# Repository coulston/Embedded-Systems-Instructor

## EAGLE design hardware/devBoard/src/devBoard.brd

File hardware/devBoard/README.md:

# Ordering Process for Development Boards

This file outlines a procedure to order development boards from [PCBWay](https://www.pcbway.com/).  
>[!NOTE] 
>These instructions referece manufacturer web pages that are not under my control.  As a 
result the web interfaces may be modified changing the look and feel of the interface.  In this
event, you will need to adapt the instructions to the current interface.

## Step 1: Verify BOM through Digikey
You will be providing PCBWay with the bill of materials (BOM) using parts
found on Digikey.  It is possible that the parts in the existing 
[BOM](https://github.com/coulston/Embedded-Systems-Instructor/blob/main/manufacture/hardware/devBoard%20BOM.xlsx) 
contains parts that are out of stock or have become obselete
since the last order.  Resolving these issues before sending the BOM to 
PCBWay will eliminate a lot of back-and-forth.

1. Login to [DigiKey](https://www.digikey.com/).
2. Start a new cart by clicking on the cart icon in the upper right corner of the web page.
3. Upload the
[BOM](https://github.com/coulston/Embedded-Systems-Instructor/blob/main/hardware/devBoard/manufacture/devBoard%20BOM.xlsx)
file via drag-and-drop of browse for BOM.

4. In the Upload File Mapping pop-up ensure that the manufacturer part number and DigiKey part number pull-downs
are selecting the correct columns of the BOM as shown in the following image.  Not as important, you may want
to select qualtity in the shown column.  In order to scoll horziontally, you will need to first scroll to the
bottom of the window using the control in the right side of the window.  Click on the Add to Current Cart
button when yoy have verified these selections.

5. If there are any issues, they will appear in the shooping cart as errors.

6. If you have obselete parts as shown, you will need to find a suitable replacement
   part from Digikey.  you must ensure that the replacement part has the same footprint, pinout and
   performs the same function as the obselete part.  Since Digikey keeps the technical documents for
   obselete parts, you should be able to get all the needed technical information
   to start this process.

## Step 2: Order from PCBWay

1. Login to [PCBWay](https://www.pcbway.com/).
2. Click on the PCB Assembly icon at the top of the page
3. In the **Assembly Service** area:
   - Quantity: Whatever you need, in this case 50.
   - Do you accept alternatives/substitutes made in China?  Yes

4. Expand **Other Parameters options**. Fill in the text boxes with the values shown below.

5. Expand **PCB Specifications options**.  Fill in the text boxes with the values shown below.
   - Size: 65.28mm x 55.83mm
   - Quantity: Match quantity in step 3.
   - Leave all the following options alone.

6. Scroll to the bottom of the page and click calculate
7. The right side of the web page will update the cost.
   - Click **Save To Cart**
   - Agree to the Special Notes

8.In the upload files pop-up
>[!NOTE] 
>The files are at the links provided.  Download the files to your local machine by clicking on the download raw file
>icon  in the upper right of the window.
- Click **Upload Gerber file** and upload. 
  [Gerber zip](https://github.com/coulston/Embedded-Systems-Instructor/blob/main/hardware/devBoard/manufacture/devBoard.zip)
- Click **Part List (BOM) Upload** and upload
  [BOM excel](https://github.com/coulston/Embedded-Systems-Instructor/blob/main/hardware/devBoard/manufacture/devBoard%20BOM.xlsx)
- Click **Upload Centroid File** and upload
  [Centroid excel](https://github.com/coulston/Embedded-Systems-Instructor/blob/main/hardware/devBoard/manufacture/devBoard%20CPL.xlsx)
- 

9. Click Submitt Order Now
10. You should hear back from the PCBWay engineers in 48 hours.

## Step 3: SD Card Holder
As ordered, the development boards do not come with the SD Cards because they are mounted to the bottom of the 
board. Hence, these have to be ordred and hand soldered using the following instructions.
1. Order 1 SD Card holder fro each development board from [DigiKey] (http://www.digikey.com) part number WM12834CT-ND
2. Solder the SD card holder
- Solder the 9 pins
- Solder the 4 mounting tabs (essential)

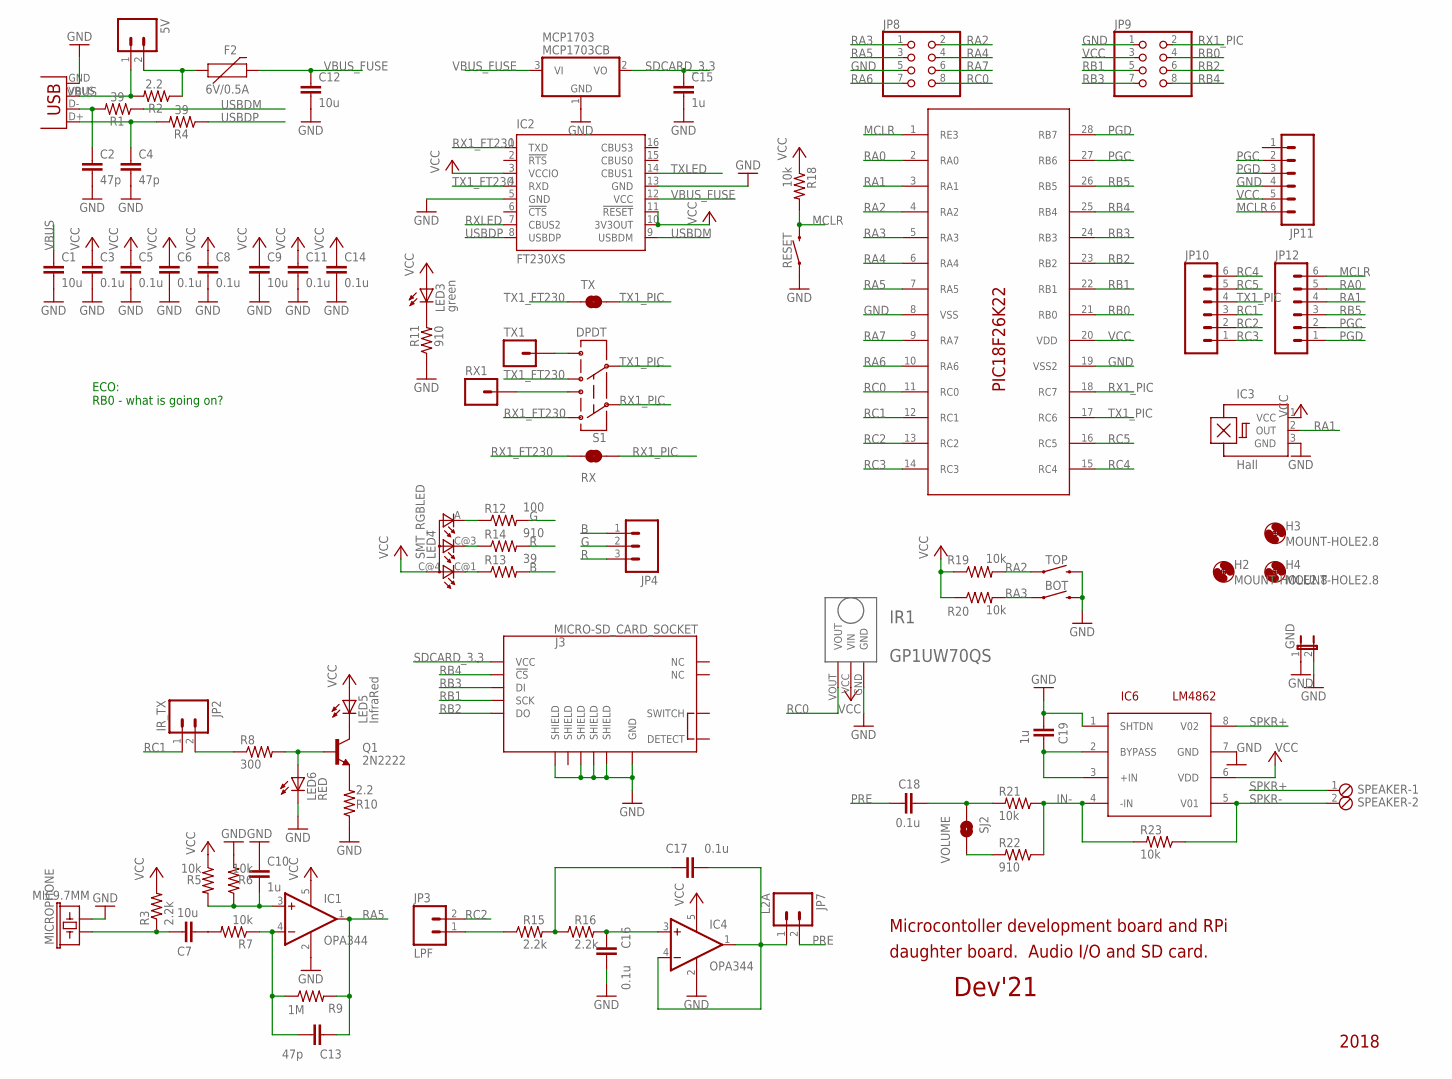
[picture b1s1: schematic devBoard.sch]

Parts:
5V: M02LOCK; 1X02_LOCK
BOT: MOMENTARY-SWITCH-SPST-SMD-5.2MM; TACTILE_SWITCH_SMD_5.2MM
C1, C7, C9, C12: 10u; C1206
C2, C4, C13: 47p; C1206
C3, C5, C6, C8, C11, C14, C16, C17, C18: 0.1u; C1206
C10, C15, C19: 1u; C1206
F2: 6V/0.5A; 1206
GND: JP1E; JP1
H2, H3, H4: MOUNT-HOLE2.8; 2,8
IC1, IC4: OPA344; SOT23-5
IC2: FT230XS; SSOP16
IC3: Hall; SOT23-W
IC6: LM4862; SO08
IR1: GP1UW70QS
J3: MICRO-SD_CARD_SOCKET; MICRO-SD-SOCKET
JP2: IR_TX; 1X02_LOCK
JP3: LPF; 1X02_LOCK
JP4: M03LOCK; 1X03_LOCK
JP7: L2A; 1X02_LOCK
JP8, JP9: PINHD-2X4; 2X04
JP10, JP11, JP12: M06LOCK; 1X06_LOCK
LED3: green; LED-1206
LED4: SMT_RGBLED; P-LCC-4
LED5: InfraRed; LED-1206
LED6: RED; LED-1206
MCP1703: MCP1703CB; SOT23
MICROPHONE: MIC9.7MM; MIC-9.7MM
PIC18F26K22: PIC18F26J2228SSOP; SSOP28DB
Q1: 2N2222; SOT23-3
R1, R4, R13: 39; R1206
R2, R10: 2.2; R1206
R3, R15, R16: 2.2k; R1206
R5, R6, R7, R18, R19, R20, R21, R23: 10k; R1206
R8: 300; R1206
R9: 1M; R1206
R11, R14, R22: 910; R1206
R12: 100; R1206
RESET: MOMENTARY-SWITCH-SPST-SMD-5.2MM; TACTILE_SWITCH_SMD_5.2MM
RX: SJ_NC; SMT-JUMPER_2_NC_TRACE_NO-SILK
RX1: M01PTH; 1X01
S1: DPDT; AYZ0202
SJ2: VOLUME; SJ_2S-NOTRACE
SPEAKER: MPT2; 2POL254
TOP: MOMENTARY-SWITCH-SPST-SMD-5.2MM; TACTILE_SWITCH_SMD_5.2MM
TX: SJ_NC; SMT-JUMPER_2_NC_TRACE_NO-SILK
TX1: M01PTH; 1X01
X1: USBSMD; USB-MINIB

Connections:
B: JP4.1, R13.2
G: JP4.2, R12.2
GND: BOT.3 (2), C1.2, C2.2, C3.2, C4.2, C5.2, C6.2, C8.2, C9.2, C10.1, C11.2, C12.2, C14.2, C15.2, C16.1, C19.2, GND.1, GND.2, IC1.2 (V-), IC2.5 (GND), IC2.13 (GND), IC3.3 (GND), IC4.2 (V-), IC6.1 (SHTDN), IC6.7 (GND), IR1.GND, J3.GND, J3.SHIELD1 (SHIELD), J3.SHIELD3 (SHIELD), J3.SHIELD4 (SHIELD), J3.SHIELD5 (SHIELD), JP8.5, JP9.1, JP11.4, LED6.C, MCP1703.1 (GND), MICROPHONE.2, PIC18F26K22.8 (VSS), PIC18F26K22.19 (VSS2), R6.2, R10.1, R11.1, RESET.1, TOP.3 (2), X1.GND
IN-: IC6.4 (-IN), R21.1, R22.1, R23.2
MCLR: JP11.6, JP12.6, PIC18F26K22.1 (RE3), R18.2, RESET.3 (2)
MIC: C13.1, IC1.4 (-IN), R7.1, R9.1
unnamed: C16.2, IC4.3 (+IN), R16.2
unnamed: C17.2, R15.2, R16.1
unnamed: C17.1, IC4.1 (OUT), IC4.4 (-IN), JP7.1
unnamed: JP3.1, R15.1
unnamed: LED4.C@3 (CBLUE), R14.1
unnamed: C2.1, R1.2, X1.D-
unnamed: C4.1, R4.2, X1.D+
unnamed: C7.1, MICROPHONE.1, R3.1
unnamed: C7.2, R7.2
unnamed: 5V.2, F2.1, R2.1
unnamed: C10.2, IC1.3 (+IN), R5.2, R6.1
unnamed: RX1.1, S1.3
unnamed: LED4.C@1 (CRED), R13.1
unnamed: LED4.A (CGREEN), R12.1
unnamed: LED5.C, Q1.3 (C)
unnamed: LED3.C, R11.2
unnamed: Q1.2 (E), R10.2
unnamed: LED6.A, Q1.1 (B), R8.2
unnamed: C19.1, IC6.2 (BYPASS), IC6.3 (+IN)
unnamed: JP2.2, R8.1
unnamed: S1.6, TX1.1
unnamed: C18.1, R21.2, SJ2.1
unnamed: R22.2, SJ2.2
PGC: JP11.2, JP12.2, PIC18F26K22.27 (RB6)
PGD: JP11.3, JP12.1, PIC18F26K22.28 (RB7)
PRE: C18.2, JP7.2
R: JP4.3, R14.2
RA0: JP12.5, PIC18F26K22.2 (RA0)
RA1: IC3.2 (OUT), JP12.4, PIC18F26K22.3 (RA1)
RA2: JP8.2, PIC18F26K22.4 (RA2), R19.2, TOP.1
RA3: BOT.1, JP8.1, PIC18F26K22.5 (RA3), R20.2
RA4: JP8.4, PIC18F26K22.6 (RA4)
RA5: C13.2, IC1.1 (OUT), JP8.3, PIC18F26K22.7 (RA5), R9.2
RA6: JP8.7, PIC18F26K22.10 (RA6)
RA7: JP8.6, PIC18F26K22.9 (RA7)
RB0: JP9.4, PIC18F26K22.21 (RB0)
RB1: J3.SCLK (SCK), JP9.5, PIC18F26K22.22 (RB1)
RB2: J3.DO, JP9.6, PIC18F26K22.23 (RB2)
RB3: J3.DI, JP9.7, PIC18F26K22.24 (RB3)
RB4: J3.CS (!CS), JP9.8, PIC18F26K22.25 (RB4)
RB5: JP12.3, PIC18F26K22.26 (RB5)
RC0: IR1.VOUT, JP8.8, PIC18F26K22.11 (RC0)
RC1: JP2.1, JP10.3, PIC18F26K22.12 (RC1)
RC2: JP3.2, JP10.2, PIC18F26K22.13 (RC2)
RC3: JP10.1, PIC18F26K22.14 (RC3)
RC4: JP10.6, PIC18F26K22.15 (RC4)
RC5: JP10.5, PIC18F26K22.16 (RC5)
RX1_FT230: IC2.1 (TXD), RX.1, S1.1
RX1_PIC: JP9.2, PIC18F26K22.18 (RC7), RX.2, S1.2
RXLED: IC2.7 (CBUS2)
SDCARD_3.3: C15.1, J3.VCC, MCP1703.2 (VO)
SPKR+: IC6.8 (V02), SPEAKER.1
SPKR-: IC6.5 (V01), R23.1, SPEAKER.2
TX1_FT230: IC2.4 (RXD), S1.4, TX.1
TX1_PIC: JP10.4, PIC18F26K22.17 (RC6), S1.5, TX.2
TXLED: IC2.14 (CBUS1)
USBDM: IC2.9 (USBDM), R1.1
USBDP: IC2.8 (USBDP), R4.1
VBUS: 5V.1, C1.1, R2.2, X1.VBUS
VBUS_FUSE: C12.1, F2.2, IC2.12 (VCC), MCP1703.3 (VI)
VCC: C3.1, C5.1, C6.1, C8.1, C9.1, C11.1, C14.1, IC1.5 (V+), IC2.3 (VCCIO), IC2.10 (3V3OUT), IC2.11 (!RESET), IC3.1 (VCC), IC4.5 (V+), IC6.6 (VDD), IR1.VCC (VIN), JP9.3, JP11.5, LED3.A, LED4.C@4 (A), LED5.A, PIC18F26K22.20 (VDD), R3.2, R5.1, R18.1, R19.1, R20.1

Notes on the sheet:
Microcontoller development board and RPi
daughter board. Audio I/O and SD card.
2018
Dev'21
ECO: RB0 - what is going on?

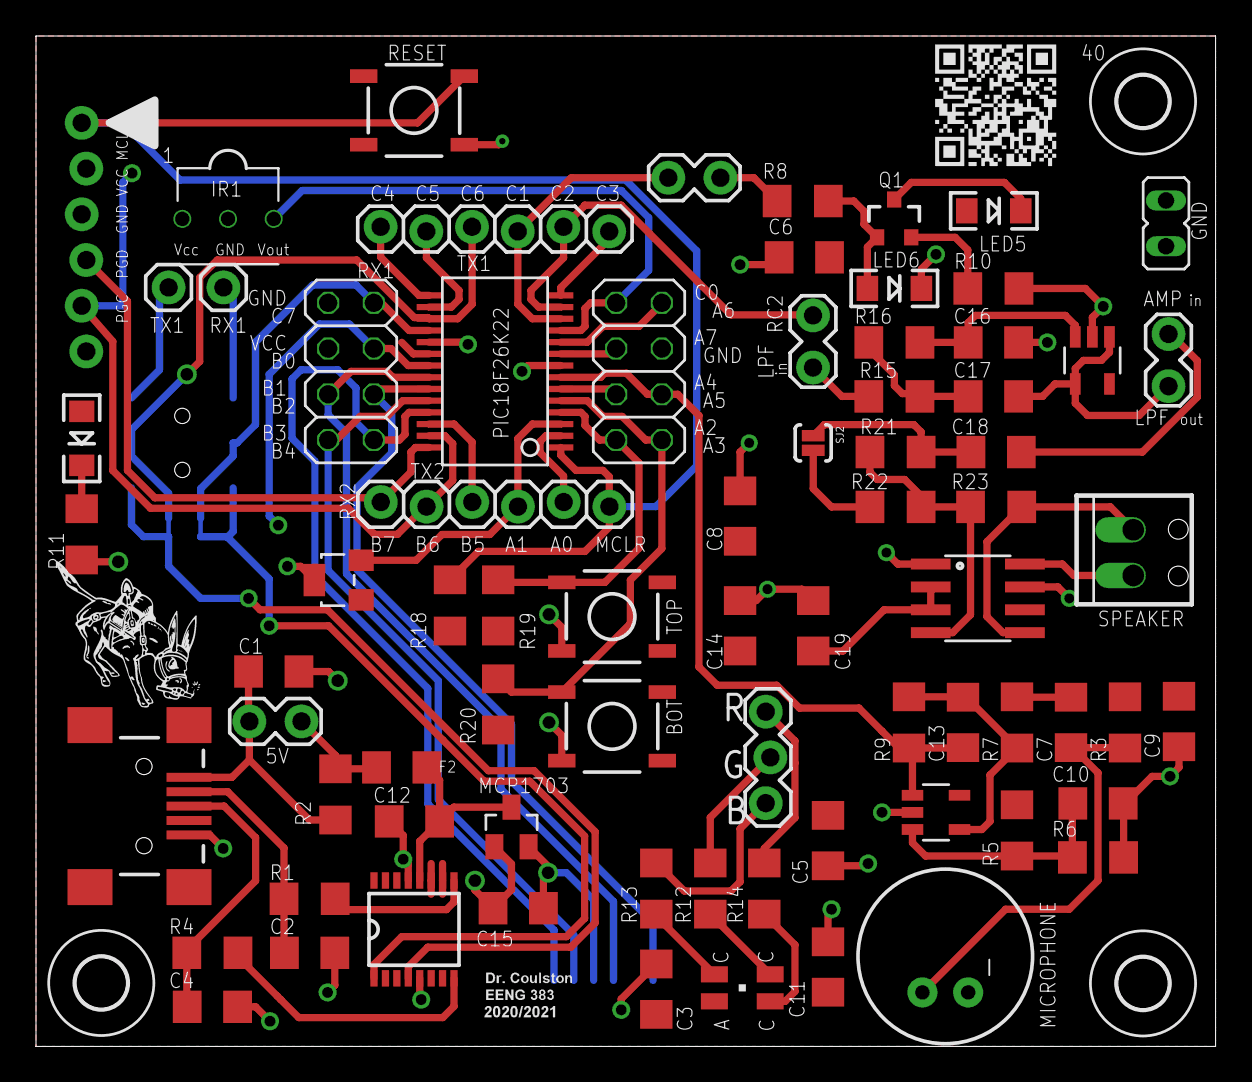
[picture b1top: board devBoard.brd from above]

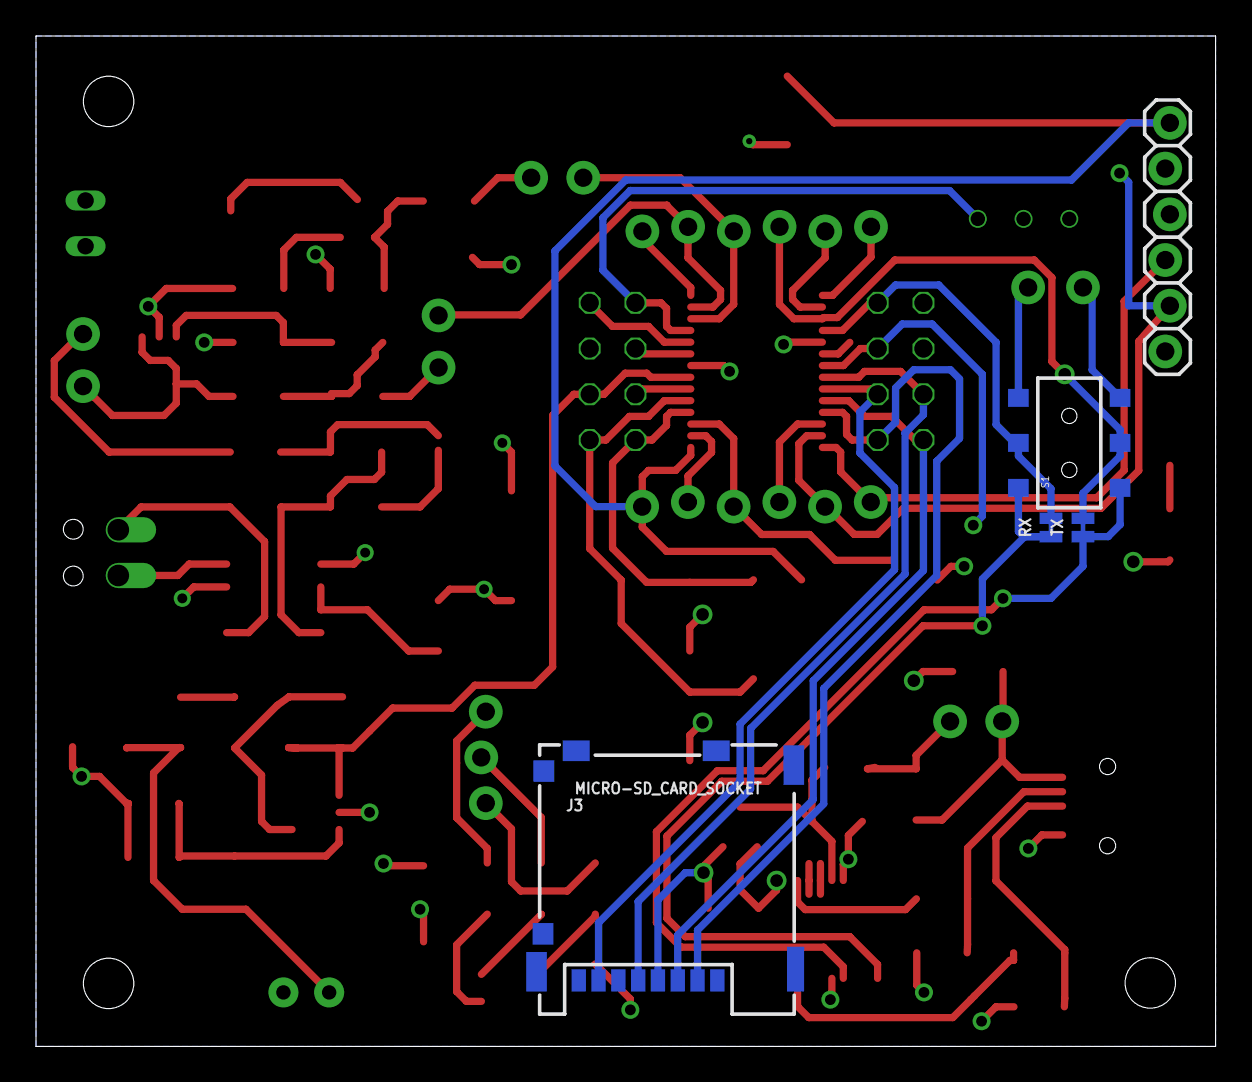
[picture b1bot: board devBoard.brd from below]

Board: 2 copper layers, 65.5 x 56.1 mm, 82 parts (5 on the bottom side), 65 nets.

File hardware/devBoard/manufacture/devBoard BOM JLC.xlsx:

Comment | Designator | Footprint | Part | Quantity
2.2 ohm | R2, R10 | 1206R | C2907445 | 1
39 ohm | R1, R4, R13 | 1206R | C25379 | 1
100 ohms | R12 | 1206R | C17901 | 1
300 ohm | R8 | 1206R | C17887 | 1
910 ohm | R11, R14, R22 | 1206R | C2930433 | 1
2.2k ohm | R3, R15, R16 | 1206R | C17948 | 1
10k ohm | R5, R6, R7, R18, R19, R20, R21, R23 | 1206R | C17902 | 1
1M ohm | R9 | 1206R | C17927 | 1
PTC fuse | F2 | 1206R | C883127 | 1
47pF | C2, C4, C13 | 1206C | C5137553 | 1
0.1uF | C3, C5, C6, C8, C11, C14, C16, C17, C18 | 1206C | C24497 | 1
1uF | C10, C15, C19 | 1206C | C1848 | 1
10uF | C1, C7, C9, C12 | 1206C | C13585 | 1
Tactile Switch SPST-NO Top Actuated Surface Mount | BOT, RESET, TOP | 5.2*5.2 | C5342990 | 1
USB | X1 | Custom | C91144 | 1
PIC 18F25K22 | PIC18F25K22 | SSOP-28 | C51680 | 1
Serial USB bridge | IC2 | SSOP-16 | C69082 | 1
GP Opamp | IC1, IC4 | SOT23-5 | C131974 | 1
2N2222 NPN | Q1 | SOT-23 |  | 1
Linear Voltage Regulator IC 1 Output 250mA SOT-23A-3 | MCP1703 | SOT-23 | C50754 | 1
Audio Amp | IC6 | SOIC-8 | C2860743 | 1
Green SM | LED3 | 1206D | C2984261 | 1
Red SM | LED6 | 1206D | C2984261 | 1
IR LED | LED5 | 1206D |  | 1
RGB LED | LED4 | PLCC-4 | C5355897 | 1
Hall Effect | IC3 | SOT-23-3 | C962159 | 1

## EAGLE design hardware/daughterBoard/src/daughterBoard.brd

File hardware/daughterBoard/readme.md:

# Ordering Process for Daughter Boards

This file outlines a procedure to order development boards from [JLCPCB](https://www.jlcpcb.com/).  
>[!NOTE] 
>These instructions referece manufacturer web pages that are not under my control.  As a 
result the web interfaces may be modified changing the look and feel of the interface.  In this
event, you will need to adapt the instructions to the current interface.

## Order from JLCPCB

1. Download [daughterBoardGerber.zip](Https://github.com/coulston/Embedded-Systems-Instructor/blob/main/hardware/daughterBoard/manufacture/daughterBoardGerber.zip) to your local drive
5. Sign In to [JLCPCB](https://www.jlcpcb.com/).
6. Click on the white Order Now button at the top of the page
7. Click on the blue Add gerber files button
8. In the pop-up, navigate and select daughterBoardGerber.zip you downloaded
9. Leave all the defaults along with the exception:
   - Quantity: Whatever you need
   - PCB Color: Blue has been the standard color
10. Click on the blue Add to Cart button
11. Click on the shopping cart icon at the top of the screen
12. Click the blue Secure Checkout button and proceed with payment and shipping.
13. You should hear back from the JLCPCB in 24 hours.

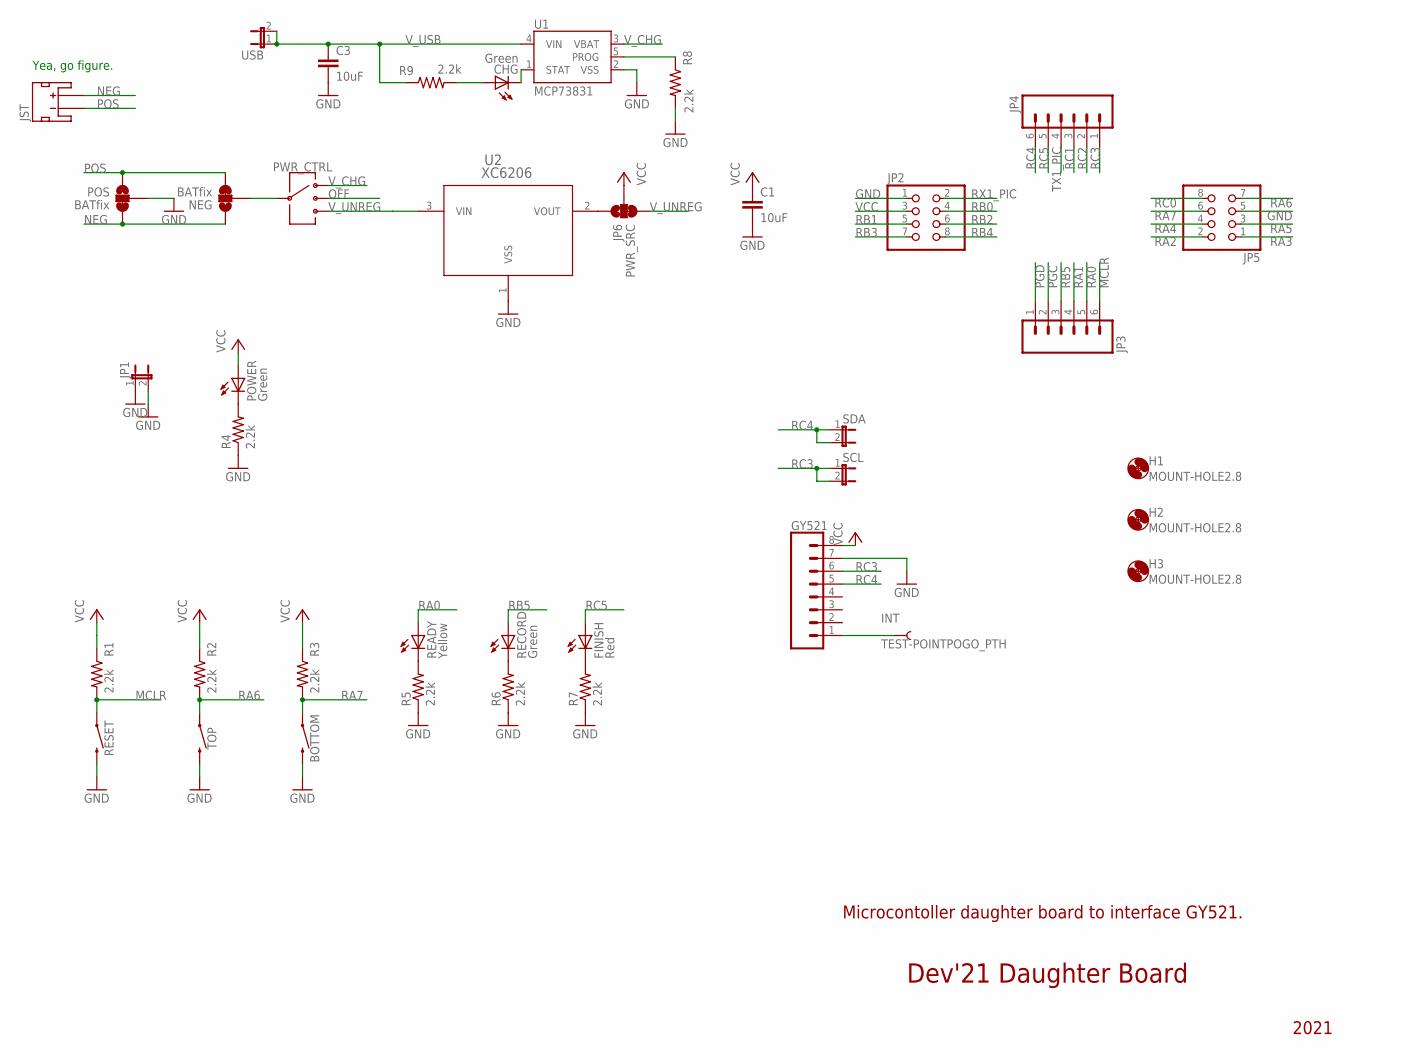
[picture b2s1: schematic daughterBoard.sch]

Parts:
BOTTOM: BOTTOM; TACTILE_SWITCH_SMD_5.2MM
C1, C3: 10uF; C1206
CHG: Green; LED-1206
FINISH: Red; LED-1206
GY521: CONN_08LOCK_LONGPADS; 1X08_LOCK_LONGPADS
H1, H2, H3: MOUNT-HOLE2.8; 2,8
INT: TEST-POINTPOGO_PTH; 1X01_NO_SILK
JP1: JP1E; JP1
JP2, JP5: PINHD-2X4; 2X04
JP3, JP4: M06LOCK; 1X06_LOCK
JP6: PWR_SRC; SMT-JUMPER_3_1-NC_TRACE_SILK
JST: JST_2MM_MALE; JST-2-SMD
NEG: BATfix; SMT-JUMPER_3_1-NC_TRACE_SILK
POS: BATfix; SMT-JUMPER_3_1-NC_TRACE_SILK
POWER: Green; LED-1206
PWR_CTRL: SWITCH-SP3T-SMD; SWITCH_SP3T_SMD
R1, R2, R3, R4, R5, R6, R7, R8, R9: 2.2k; R1206
READY: Yellow; LED-1206
RECORD: Green; LED-1206
RESET: RESET; TACTILE_SWITCH_SMD_5.2MM
SCL: JUMPER-2PTH_LOCK; 1X02_LOCK
SDA: JUMPER-2PTH_LOCK; 1X02_LOCK
TOP: TOP; TACTILE_SWITCH_SMD_5.2MM
U1: MCP73831; SOT23-5
U2: XC6206; SOT-23_TOR-M
USB: JUMPER-2PTH_LOCK; 1X02_LOCK

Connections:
GND: BOTTOM.3 (2), C1.2, C3.2, GY521.7, JP1.1, JP1.2, JP2.1, JP5.5, POS.2, R4.1, R5.1, R6.1, R7.1, R8.2, RESET.3 (2), TOP.3 (2), U1.2 (VSS), U2.1 (VSS)
MCLR: JP3.6, R1.2, RESET.1
unnamed: NEG.2, PWR_CTRL.3
unnamed: R6.2, RECORD.C
unnamed: R5.2, READY.C
unnamed: FINISH.C, R7.2
unnamed: POWER.C, R4.2
unnamed: GY521.1, INT.1
unnamed: JP6.1, U2.2 (VOUT)
unnamed: CHG.A, R9.2
unnamed: R8.1, U1.5 (PROG)
unnamed: CHG.C, U1.1 (STAT)
NEG: JST.2 (+), NEG.1, POS.3
OFF: PWR_CTRL.2
PGC: JP3.2
PGD: JP3.1
POS: JST.1 (-), NEG.3, POS.1
RA0: JP3.5, READY.A
RA1: JP3.4
RA2: JP5.2
RA3: JP5.1
RA4: JP5.4
RA5: JP5.3
RA6: JP5.7, R2.2, TOP.1
RA7: BOTTOM.1, JP5.6, R3.2
RB0: JP2.4
RB1: JP2.5
RB2: JP2.6
RB3: JP2.7
RB4: JP2.8
RB5: JP3.3, RECORD.A
RC0: JP5.8
RC1: JP4.3
RC2: JP4.2
RC3: GY521.6, JP4.1, SCL.1, SCL.2
RC4: GY521.5, JP4.6, SDA.1, SDA.2
RC5: FINISH.A, JP4.5
RX1_PIC: JP2.2
TX1_PIC: JP4.4
VCC: C1.1, GY521.8, JP2.3, JP6.2, POWER.A, R1.1, R2.1, R3.1
V_CHG: PWR_CTRL.1, U1.3 (VBAT)
V_UNREG: JP6.3, PWR_CTRL.4, U2.3 (VIN)
V_USB: C3.1, R9.1, U1.4 (VIN), USB.1, USB.2

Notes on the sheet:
Microcontoller daughter board to interface GY521.
2021
Dev'21 Daughter Board
Yea, go figure.

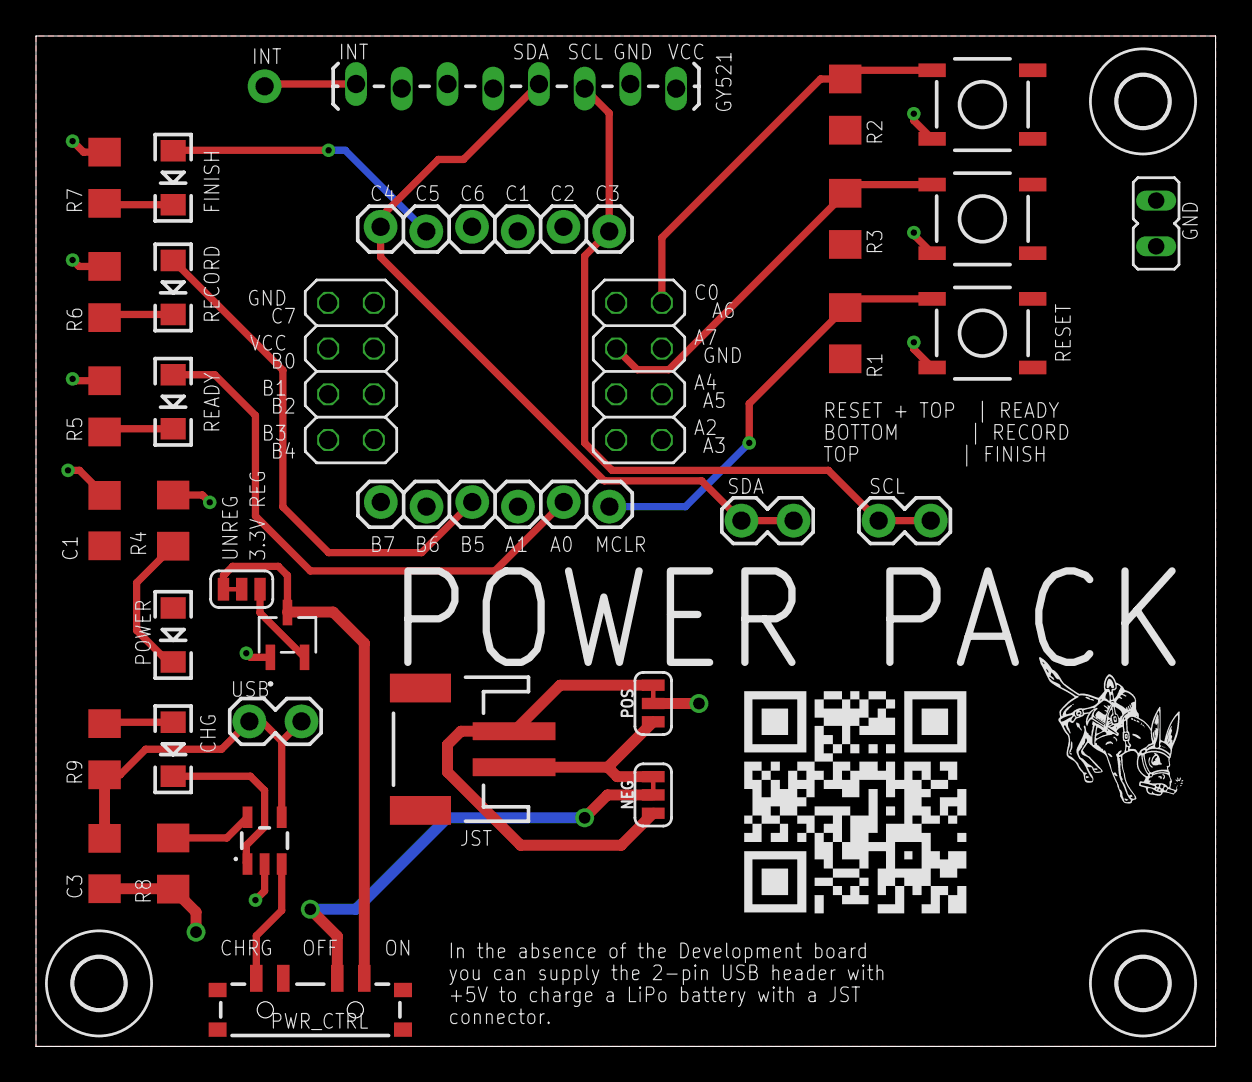
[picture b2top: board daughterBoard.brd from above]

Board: 2 copper layers, 65.5 x 56.1 mm, 39 parts (0 on the bottom side), 25 nets.

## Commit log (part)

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2025-06-04 Added Manufacturing Files
2025-06-04 Create README.md
    Walks users through the process of ordering assembled development boards from PCBWay
2025-06-04 Adding some images for the README
2025-06-04 pcbWay images to Order
2025-06-04 some updates
2025-06-05 Added Daughter Board
    Cleared up directory structure and added daughter board folder and files
2025-06-05 Create .gitignore
    Ignore for EAGLE CAD revision files
2025-06-05 Create .gitignore
    EAGLE CAD backup files
2025-06-05 Added cam and dru
    added files so that you can remake the gerber files using the same set of design rules and layers
2025-06-05 update gerber file names
2025-06-06 updating BOM
    Will stop this until I get the SD Card information
2025-06-09 Add Testing Procedure
2025-06-11 Update README.md
    Fixed broken links due to change in directory name
2025-06-12 Update devBoard BOM.xlsx
    Removed the LCSC and JLCPCB columns from the inclusive page. Removed other pages from the BOM.
2025-06-16 Update devBoard BOM.xlsx
    Change the number of 0.l1uF capacitors to 9 instead of the listed 7.
2025-07-10 Update devBoard CPL.xlsx
    Added the positions for the SMT parts in a second tab.
2025-10-06 Add PPT
    Created by Hisham Sager based on the course materials created by Christopher Coulston
2026-04-20 Added QR code
    Added coulston.github.io QR code to the Daughter board
2026-04-20 Updated the source files
2026-04-28 Update README.md
    Fixed broken links

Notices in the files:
parts and their libraries:
SparkFun-Switches: Licensing: Creative Commons ShareAlike 4.0 International - https://creativecommons.org/licenses/by-sa/4.0
COPYRIGHT: Copyright (C) 2021 Ultra Librarian. All rights reserved.
